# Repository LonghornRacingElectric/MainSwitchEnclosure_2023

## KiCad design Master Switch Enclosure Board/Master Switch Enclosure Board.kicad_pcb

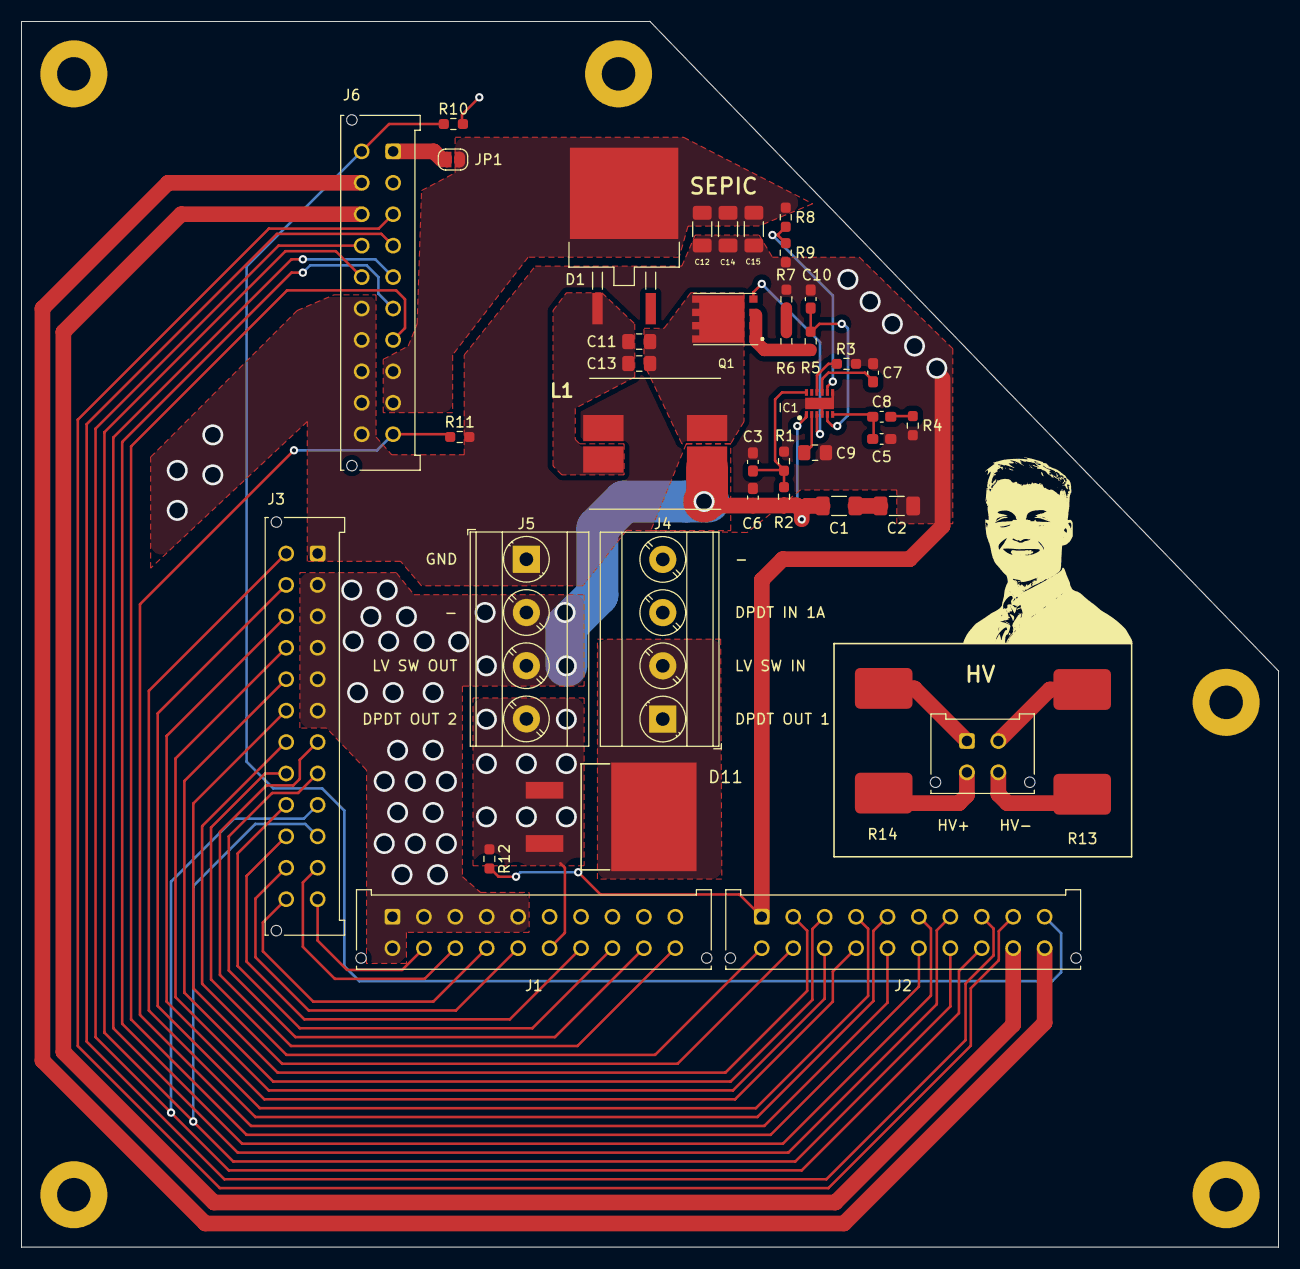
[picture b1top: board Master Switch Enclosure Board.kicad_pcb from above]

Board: 2 copper layers, 120.0 x 117.0 mm, 46 parts (0 on the bottom side), 52 nets.

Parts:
C1, C2, C12, C14, C15: 22u; C_1206_3216Metric_Pad1.33x1.80mm_HandSolder
C3, C10: 100p; C_0603_1608Metric_Pad1.08x0.95mm_HandSolder
C5: 270p; C_0603_1608Metric_Pad1.08x0.95mm_HandSolder
C6: 100n; C_0603_1608Metric_Pad1.08x0.95mm_HandSolder
C7: 220n; C_0603_1608Metric_Pad1.08x0.95mm_HandSolder
C8: 6.8n; C_0603_1608Metric_Pad1.08x0.95mm_HandSolder
C9: 1u; C_0805_2012Metric_Pad1.18x1.45mm_HandSolder
C11, C13: 4.7u; C_0805_2012Metric_Pad1.18x1.45mm_HandSolder
D1: STPS20M100SG-TR
D11: D_Schottky; MBRB41H100CTT4G
IC1: LM5155DSSR; SON50P200X300X80-13N-D
J1: Harness In A; Molex_Micro-Fit_3.0_43045-2012_2x10_P3.00mm_Vertical
J2: Harness In B; Molex_Micro-Fit_3.0_43045-2012_2x10_P3.00mm_Vertical
J3: Harness Out; Molex_Micro-Fit_3.0_43045-2412_2x12_P3.00mm_Vertical
J4, J5: Screw_Terminal_01x04; TerminalBlock_Phoenix_MKDS-3-4-5.08_1x04_P5.08mm_Horizontal
J6: 20-pin MicroFit; Molex_Micro-Fit_3.0_43045-2012_2x10_P3.00mm_Vertical
J7: 4-pin MicroFit; Molex_Micro-Fit_3.0_43045-0412_2x02_P3.00mm_Vertical
JP1: Jumper; SolderJumper-2_P1.3mm_Open_RoundedPad1.0x1.5mm
L1: 7448700015; WE-DD_12XX_CROSSED12
M1, M2, M3, M4, M5: MountingHole_3.2mm_M3_Pad
Q1: CSD18537NQ5A; CSD19531Q5AT
R1: 6k8; R_0603_1608Metric_Pad0.98x0.95mm_HandSolder
R2: 34k8; R_0603_1608Metric_Pad0.98x0.95mm_HandSolder
R3: 17k8; R_0603_1608Metric_Pad0.98x0.95mm_HandSolder
R4: 10k; R_0603_1608Metric_Pad0.98x0.95mm_HandSolder
R5: 100; R_0603_1608Metric_Pad0.98x0.95mm_HandSolder
R6, R7: 4m; R_0603_1608Metric_Pad0.98x0.95mm_HandSolder
R8: 51k1; R_0603_1608Metric_Pad0.98x0.95mm_HandSolder
R9: 4k7; R_0603_1608Metric_Pad0.98x0.95mm_HandSolder
R10, R12: 100k; R_0603_1608Metric_Pad0.98x0.95mm_HandSolder
R11: 15k; R_0603_1608Metric_Pad0.98x0.95mm_HandSolder
R13, R14: 15k; 355015KFT

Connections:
/SEPIC/COMP: C5.1, C8.1, IC1.6 (COMP)
/SEPIC/FB: IC1.8 (FB), R8.2, R9.1
/SEPIC/RT: IC1.10 (RT), R3.2
/SEPIC/SS: C7.1, IC1.9 (SS)
/SEPIC/UVLO: C3.1, IC1.12 (UVLO/SYNC), R1.1, R2.2
BSPDTest_in: J2.7, J6.5
BSPDTest_out: J2.6, J6.6
BYP_out: D11.2 (A), J1.16, J5.4, R12.1
CANH_EM: J2.9, J6.3
CANH_Tel: J1.18, J3.21
CANH_VCU1: J2.18, J3.9, J6.14
CANH_VCU2: J1.13, J3.11
CANH_VCU3: J2.5, J3.13
CANH_VCU4: J2.14, J3.15
CANH_ret_Tel: J1.15, J3.23
CANH_ret_VCU2: J2.3, J3.17
CANH_ret_VCU3: J2.12, J3.19
CANL_EM: J2.8, J6.4
CANL_Tel: J1.17, J3.22
CANL_VCU1: J2.17, J3.10, J6.15
CANL_VCU2: J1.12, J3.12
CANL_VCU3: J2.4, J3.14
CANL_VCU4: J2.13, J3.16
CANL_ret_Tel: J1.14, J3.24
CANL_ret_VCU2: J2.2, J3.18
CANL_ret_VCU3: J2.11, J3.20
CHRG_in: J2.10, J6.11, R10.1
EM_12V: J6.1, JP1.2 (B)
GND: C2.2, C3.2, C5.2, C6.2, C7.2, C9.1, C10.1, C12.2, C14.2, C15.2, IC1.4 (PGND), IC1.7 (AGND), IC1.13 (EP), J2.1, J3.1, J5.1, J6.2, J6.16, J6.17, J6.18, J6.19, J6.20, L1.3, M1.1, M2.1, M3.1, M4.1, M5.1, R1.2, R3.1, R4.2, R7.2, R9.2, R10.2, R11.2, R12.2
HV+: J7.1, R14.2
HV-: J7.2, R13.2
LVBAT_in: J1.6, J1.7, J1.8, J1.9, J1.10, J4.3, J4.4
LVBAT_sw: D11.1 (K), J4.1, J4.2
LV_mastersw_out: C1.1, C6.1, IC1.1 (BIAS), J1.1, J1.2, J1.3, J1.4, J1.5, J1.11, J3.2, J3.3, J3.4, J3.5, J3.6, J5.2, J5.3, L1.1, R2.1
unnamed: C1.2, C2.1
unnamed: C8.2, R4.1
unnamed: C9.2, IC1.2 (VCC)
unnamed: C10.2, IC1.5 (CS), R5.2
unnamed: C11.1, C13.1, D1.1, L1.4
unnamed: C11.2, C13.2, L1.2, Q1.5 (D_1), Q1.6 (D_2), Q1.7 (D_3), Q1.8 (D_4)
unnamed: IC1.3 (GATE), Q1.4 (G)
unnamed: J7.3, R14.1
unnamed: J7.4, R13.1
unnamed: Q1.1 (S_1), Q1.2 (S_2), Q1.3 (S_3), R5.1, R6.1
unnamed: R6.2, R7.1
RST_out: J2.15, J6.10, R11.1
SEPIC_out: C12.1, C14.1, C15.1, D1.3, J6.8, J6.9, JP1.1 (A), R8.1
SHDN2_in: J2.19, J6.13
SHDN2_out: J2.20, J6.12
TSALEnergized_pt: J1.19, J3.8
TSALSafe_pt: J1.20, J3.7
VCUWake_out: J2.16, J6.7

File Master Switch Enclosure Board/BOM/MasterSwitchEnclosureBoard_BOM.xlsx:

ID | Notes | Name | Designator | Quantity | JLCPCB Designation | Supplier | Supplier Part # | Manufacturer | Manufacturer Part # | Price | Total Price
1 | SEPIC | 4.7uF 0805 | C11,C13 | 2 | Basic | LCSC | C1779 | Samsung Electro-Mechanics | CL21A475KAQNNNE | 1.0500000000000001E-2 | 2.1000000000000001E-2
2 | SEPIC | 22uF 1206 | C12,C14,C15,C1,C2 | 3 | Basic | LCSC | C12891 | Samsung Electro-Mechanics | CL31A226KAHNNNE | 0.05 | 0.15000000000000002
3 | SEPIC | 100pF 0603 | C3,C10 | 2 | Basic | LCSC | C14858 | Samsung Electro-Mechanics | CL10C101JB8NNNC | 4.1000000000000003E-3 | 8.2000000000000007E-3
4 | SEPIC | 270pF 0603 | C5 | 1 | - | Mouser | 603-CC603KRX7R9BB271 | YAGEO | CC0603KRX7R9BB271 | 0.1 | 0.1
5 | SEPIC | 100nF 0603 | C6 | 1 | Basic | LCSC | C14663 | YAGEO | CC0603KRX7R9BB104 | 2.0999999999999999E-3 | 2.0999999999999999E-3
6 | SEPIC | 220nF 0603 | C7 | 1 | Basic | LCSC | C21120 | Samsung Electro-Mechanics | CL10B224KA8NNNC | 5.0000000000000001E-3 | 5.0000000000000001E-3
7 | SEPIC | 6.8nF 0603 | C8 | 1 | Basic | LCSC | C1631 | FH (Guangdong Fenghua Advanced Tech) | 0603B682K500NT | 2.8999999999999998E-3 | 2.8999999999999998E-3
8 | SEPIC | 1uF 0805 | C9 | 1 | Basic | LCSC | C28323 | Samsung Electro-Mechanics | CL21B105KBFNNNE | 8.2000000000000007E-3 | 8.2000000000000007E-3
9 | SEPIC | Schottky Diode | D1 | 1 | - | Mouser | 511-STPS20M100SG-TR | STMicroelectronics | STPS20M100SG-TR | 3.22 | 3.22
10 | SEPIC | Inductor | L1 | 1 | - | Mouser | 710-7448700015 | Wurth Elektronik | 7448700015 | 2.81 | 2.81
11 | SEPIC | MOSFET | Q1 | 1 | Extended | LCSC | C72266 | Texas Instruments | CSD18537NQ5A | 3.8247 | 3.8247
12 | SEPIC | 6.8kΩ 0603 | R1 | 1 | Basic | LCSC | C23212 | UNI-ROYAL | 0603WAF6801T5E | 1E-3 | 1E-3
13 | SEPIC | 34.8kΩ 0603 | R2 | 1 | - | Mouser | 71-CRCW0603-34.8K | Vishay / Dale | CRCW060334K8FKTA | 0.15 | 0.15
14 | SEPIC | 17.8kΩ 0603 | R3 | 1 | - | Mouser | 71-CRCW0603-17.8K-E3 | Vishay / Dale | CRCW060317K8FKEA | 0.1 | 0.1
15 | SEPIC | 10kΩ 0603 | R4 | 1 | - | Mouser | C25804 | UNI-ROYAL | 0603WAF1002T5E | 8.9999999999999998E-4 | 8.9999999999999998E-4
16 | SEPIC | 100Ω 0603 | R5 | 1 | - | Mouser | C22775 | UNI-ROYAL | 0603WAF1000T5E | 1E-3 | 1E-3
17 | SEPIC | 4mΩ 0603 | R6,R7 | 2 | - | Mouser | 71-WFCP06034L000FE66 | Vishay | WFCP06034L000FE66 | 0.64 | 1.28
18 | SEPIC | 51.1kΩ 0603 | R8 | 1 |  | Mouser | 71-CRCW020151K1FKED | Vishay / Dale | CRCW020151K1FKED | 0.28000000000000003 | 0.28000000000000003
19 | SEPIC | 4.7kΩ 0603 | R9 | 1 | Basic | LCSC | C23162 | UNI-ROYAL | 0603WAF4701T5E | 1E-3 | 1E-3
20 | pull-down | 100kΩ 0603 | R10,R12 | 2 | Basic | LCSC | C25803 | UNI-ROYAL | 0603WAF1003T5E | 1.1000000000000001E-3 | 2.2000000000000001E-3
21 | pull-down | 15kΩ 0603 | R11 | 1 | Basic | LCSC | C22809 | UNI-ROYAL | 0603WAF1502T5E | 1E-3 | 1E-3
22 | for LV bypass signal | Schottky Diode | D11 | 1 | - | Mouser | 771-WNS40H100CBJ | WeEn Semiconductors | WNS40H100CBJ | 1.6 | 1.6
23 | for high current | 1x4 Screw Terminal | J5,J4 | 2 | - | Mouser | 651-1712805 | Phoenix Contact | 1712805 | 4.46 | 8.92

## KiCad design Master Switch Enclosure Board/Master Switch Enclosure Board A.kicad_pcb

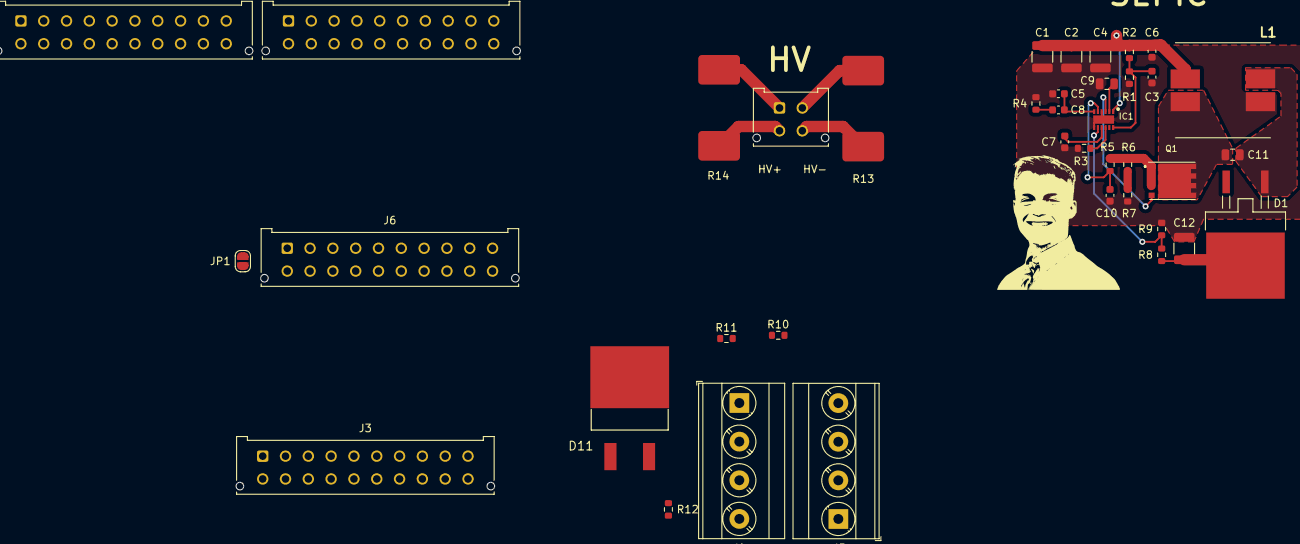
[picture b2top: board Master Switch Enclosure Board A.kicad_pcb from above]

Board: 2 copper layers, 39 parts (0 on the bottom side), 47 nets.

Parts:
C1, C2, C4: 10u; C_1210_3225Metric
C3, C10: 100p; C_0603_1608Metric
C5: 270p; C_0603_1608Metric
C6: 100n; C_0603_1608Metric
C7: 220n; C_0603_1608Metric
C8: 6.8n; C_0603_1608Metric
C9: 1u; C_0805_2012Metric
C11: 9.4u; C_0805_2012Metric
C12: 66u; C_1210_3225Metric
D1: STPS20M100SG-TR
D11: D_Schottky; MBRB41H100CTT4G
IC1: LM5155DSSR; SON50P200X300X80-13N-D
J1: Harness In A; Molex_Micro-Fit_3.0_43045-2012_2x10_P3.00mm_Vertical
J2: Harness In B; Molex_Micro-Fit_3.0_43045-2012_2x10_P3.00mm_Vertical
J3: Harness Out; Molex_Micro-Fit_3.0_43045-2012_2x10_P3.00mm_Vertical
J4, J5: Screw_Terminal_01x04; TerminalBlock_Phoenix_MKDS-3-4-5.08_1x04_P5.08mm_Horizontal
J6: 20-pin MicroFit; Molex_Micro-Fit_3.0_43045-2012_2x10_P3.00mm_Vertical
J7: 4-pin MicroFit; Molex_Micro-Fit_3.0_43045-0412_2x02_P3.00mm_Vertical
JP1: Jumper; SolderJumper-2_P1.3mm_Open_RoundedPad1.0x1.5mm
L1: 7448700015; WE-DD_12XX_CROSSED12
Q1: CSD18537NQ5A; CSD19531Q5AT
R1: 6k8; R_0603_1608Metric
R2: 34k8; R_0603_1608Metric
R3: 17k8; R_0603_1608Metric
R4: 10k; R_0603_1608Metric
R5: 100; R_0603_1608Metric
R6, R7: 4m; R_0603_1608Metric
R8: 51k1; R_0603_1608Metric
R9: 4k7; R_0603_1608Metric
R10, R12: 100k; R_0603_1608Metric
R11: 15k; R_0603_1608Metric
R13, R14: 15k; 355015KFT

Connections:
/SEPIC/COMP: C5.1, C8.1, IC1.6 (COMP)
/SEPIC/FB: IC1.8 (FB), R8.2, R9.1
/SEPIC/RT: IC1.10 (RT), R3.2
/SEPIC/SS: C7.1, IC1.9 (SS)
/SEPIC/UVLO: C3.1, IC1.12 (UVLO/SYNC), R1.1, R2.2
BSPDTest_in: J2.18, J6.5
BSPDTest_out: J2.19, J6.6
BYP_out: D11.2 (A), J1.15, J4.2, R12.1
CANH_EM: J1.19, J6.3
CANH_VCU1: J2.5, J3.8, J6.15
CANH_VCU2: J2.7, J3.10
CANH_VCU3: J2.9, J3.12
CANH_VCU4: J2.11, J3.14
CANH_ret_VCU2: J2.13, J3.16
CANH_ret_VCU3: J2.15, J3.18
CANL_EM: J1.20, J6.4
CANL_VCU1: J2.6, J3.9, J6.14
CANL_VCU2: J2.8, J3.11
CANL_VCU3: J2.10, J3.13
CANL_VCU4: J2.12, J3.15
CANL_ret_VCU2: J2.14, J3.17
CANL_ret_VCU3: J2.16, J3.19
CHRG_in: J1.16, J6.9, R10.1
EM_12V: J6.1, JP1.2 (B)
GND: C1.2, C2.2, C3.2, C4.2, C5.2, C6.2, C7.2, C9.1, C10.1, C12.2, IC1.4 (PGND), IC1.7 (AGND), IC1.13 (EP), J2.17, J3.20, J4.4, J5.1, J5.2, J6.2, J6.16, J6.17, J6.18, J6.19, J6.20, L1.3, R1.2, R3.1, R4.2, R7.2, R9.2, R10.2, R11.2, R12.2
HV+: J7.1, R14.2
HV-: J7.2, R13.2
LVBAT_in: J1.1, J1.2, J1.3, J1.4, J1.5, J4.3
LVBAT_sw: D11.1 (K), J4.1, J5.4
LV_mastersw_out: C1.1, C2.1, C4.1, C6.1, IC1.1 (BIAS), J1.6, J1.7, J1.8, J1.9, J1.10, J1.11, J3.1, J3.2, J3.3, J3.4, J3.5, J5.3, L1.1, R2.1
unnamed: C8.2, R4.1
unnamed: C9.2, IC1.2 (VCC)
unnamed: C10.2, IC1.5 (CS), R5.2
unnamed: C11.1, D1.1, L1.4
unnamed: C11.2, L1.2, Q1.5 (D_1), Q1.6 (D_2), Q1.7 (D_3), Q1.8 (D_4)
unnamed: IC1.3 (GATE), Q1.4 (G)
unnamed: J7.3, R14.1
unnamed: J7.4, R13.1
unnamed: Q1.1 (S_1), Q1.2 (S_2), Q1.3 (S_3), R5.1, R6.1
unnamed: R6.2, R7.1
RST_out: J1.14, J6.8, R11.1
SEPIC_out: C12.1, D1.3, J6.7, J6.10, JP1.1 (A), R8.1
SHDN2_in: J1.12, J6.13
SHDN2_out: J1.13, J6.12
TSALEnergized_pt: J1.18, J3.7
TSALSafe_pt: J1.17, J3.6
VCUWake_out: J2.20, J6.11

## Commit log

2022-11-28 split schematic in two
2022-12-02 schematics ready for review
2022-12-04 resolved error reset requirements
2022-12-08 PCB partial layout
2022-12-29 tsmp tanky resistor
2023-01-02 remove second board
2023-01-02 renames
2023-01-07 finished routing
2023-01-08 less resistance, more spacing
2023-01-08 done
2023-01-09 bom sheets
2023-01-09 ready to order i think

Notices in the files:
parts and their libraries:
Copyright 2021 Accelerated Designs. All rights reserved.
